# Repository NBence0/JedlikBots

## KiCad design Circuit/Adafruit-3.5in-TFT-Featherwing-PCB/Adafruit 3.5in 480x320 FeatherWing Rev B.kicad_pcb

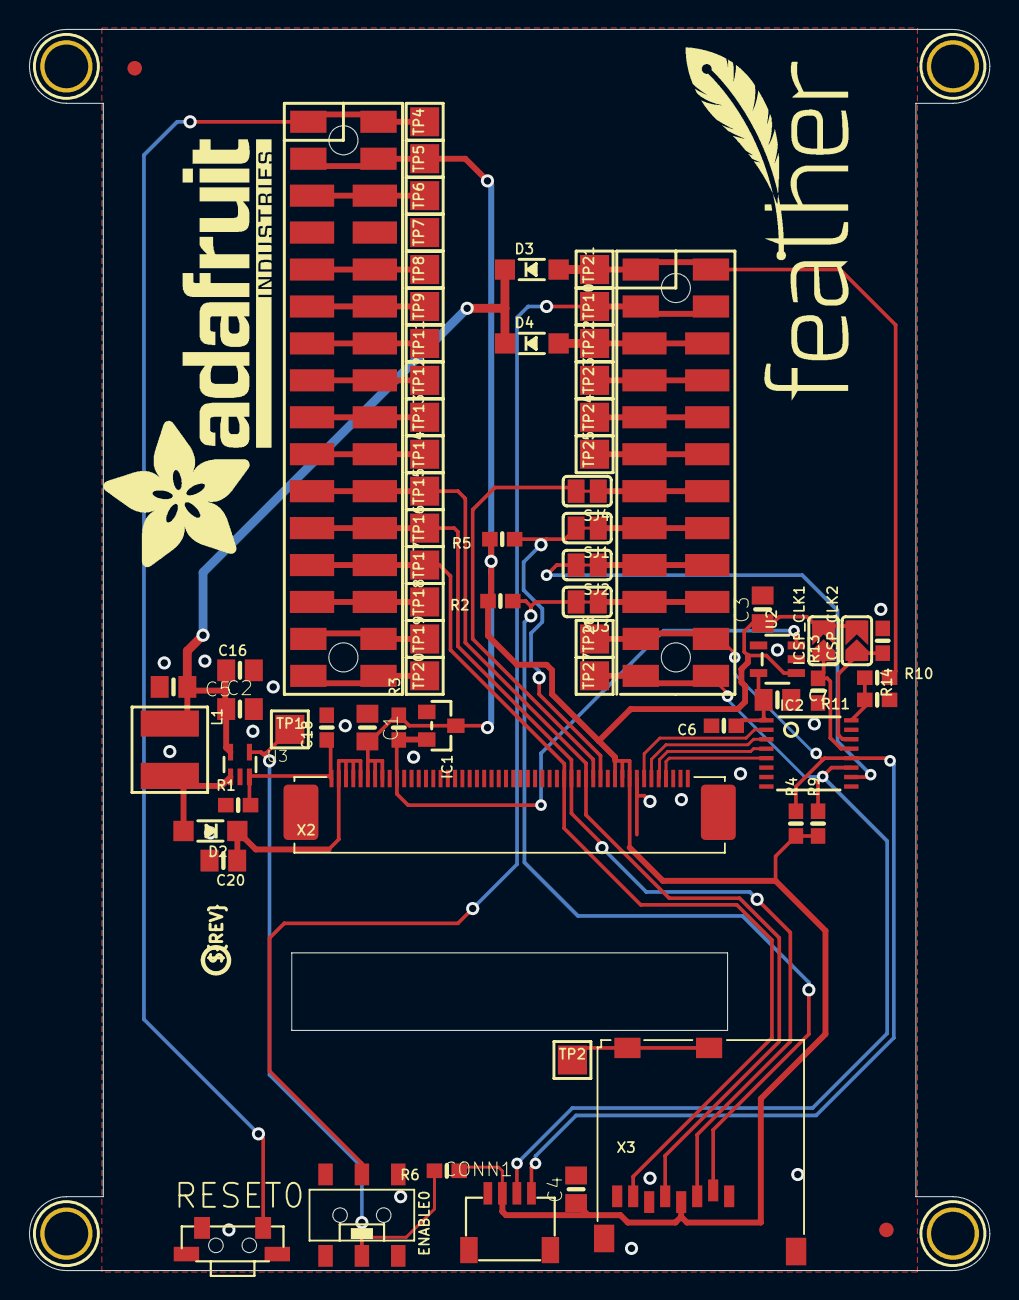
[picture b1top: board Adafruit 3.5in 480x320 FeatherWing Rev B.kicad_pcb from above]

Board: 16 copper layers, 66.0 x 85.3 mm, 92 parts (1 on the bottom side), 47 nets.

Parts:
C1, C16, C20: 1uF; 0805-NO
C2, C3, C4, C5, C7: 10uF; 0805-NO
C6, C18: 0.1uF; 0603-NO
CONN1: STEMMA_I2C_QT; JST_SH4
D2, D3, D4: MBR0540; SOD-123
ENABLE0: Slide Switch; EG1390
IC1: RESET_SUPERVISORAPX80X_SA; SOT23-WIDE
IC2: TSC2007PW; TSSOP16
ICSP_CLK1: A1; SOLDERJUMPER_ARROW_NOPASTE
ICSP_CLK2: A0; SOLDERJUMPER_ARROW_NOPASTE
L1: 6.8uH; INDUCTOR_5X5MM_NR5040_NOTHERMALS
MS2: FEATHERWING_SMTDUAL; FEATHERWING_SMT2
PLABEL0: PLABEL0
PLABEL1: PLABEL1
PLABEL2: PLABEL2
PLABEL3: PLABEL3
PLABEL4: PLABEL4
PLABEL5: PLABEL5
PLABEL6: PLABEL6
PLABEL7: PLABEL7
PLABEL8: PLABEL8
PLABEL9: PLABEL9
PLABEL10: PLABEL10
PLABEL11: PLABEL11
PLABEL12: PLABEL12
PLABEL13: PLABEL13
PLABEL14: PLABEL14
PLABEL15: PLABEL15
R1: 8.2 ohm; 0603-NO
R2, R5, R6, R10, R11: 100K; 0603-NO
R3, R4, R9, R13, R14: 10K; 0603-NO
RESET0: SPST_RA; SPST_TACTILE_RA
SJ1, SJ2, SJ3, SJ4: SOLDERJUMPER_CLOSEDWIRE
TP1, TP2, TP4, TP5, TP6, TP7, TP8, TP9, TP10, TP11, TP12, TP13, TP14, TP15, TP16, TP17, TP18, TP19, TP20, TP21, TP22, TP23, TP24, TP25, TP26, TP27: TESTPOINT_PAD_2MM
U2: AP2127K-3.3; SOT23-5
U3: TPS61169; SC70-5
U$7, U$15, U$16, U$17: MOUNTINGHOLE3.0THIN; MOUNTINGHOLE_3.0_PLATEDTHIN
U$9, U$23: FIDUCIAL_1MM
U$11: FEATHERLOGO
U$19: ADAFRUIT_TEXT_30MM
U$37: PCBFEAT-REV-040
X2: 3.5" TFT; TFT_3.5IN_320X480_50PIN
X3: MicroSD; MICROSD

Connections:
3.3V: C1.1, C3.1, C4.1, CONN1.2, IC1.3, ICSP_CLK1.2, ICSP_CLK2.2, MS2.2, MS2.2', R2.2, R3.2, R4.1, R5.2, R6.1, R9.1, TP5.P$1, U2.1, X2.6, X2.7, X2.8, X2.40, X2.41, X2.42, X3.4
+5V: C2.1, C5.1, C16.1, D3.C, D4.C, L1.P$1, U3.5
+24V: C20.1, D2.C, X2.2, X2.3, X2.4, X2.5
A: MS2.5, MS2.5', TP8.P$1
ADDR0: IC2.14, ICSP_CLK2.1, R14.2
ADDR1: IC2.13, ICSP_CLK1.1, R13.2
AREF: MS2.3, MS2.3', TP6.P$1
AUX: IC2.16, R10.1, R11.2
B: MS2.6, MS2.6', TP9.P$1
C: MS2.7, MS2.7', TP11.P$1
CARDDET: TP2.P$1, X3.CD1, X3.CD2
D: MS2.8, MS2.8', TP12.P$1
E: MS2.9, MS2.9', TP13.P$1
EN: ENABLE0.P2, MS2.27, MS2.27', TP10.P$1
F: MS2.10, MS2.10', TP14.P$1
G: MS2.16, MS2.16', TP20.P$1
GND: C1.2, C2.2, C3.2, C4.2, C5.2, C6.2, C7.2, C16.2, C18.2, C20.2, CONN1.1, CONN1.MT1, CONN1.MT2, ENABLE0.S1, ENABLE0.S2, IC1.1, IC2.6, MS2.4, MS2.4', R1.1, R11.1, R13.1, R14.1, RESET0.1, RESET0.MT1, RESET0.MT2, TP7.P$1, U2.2, U3.2, X2.43, X2.48, X2.49, X2.50, X3.6, X3.MT1, X3.MT2
H: MS2.19, MS2.19', SJ3.1
I: MS2.20, MS2.20', SJ2.1
J: MS2.21, MS2.21', SJ1.1
K: MS2.22, MS2.22', SJ4.1
L: MS2.23, MS2.23', TP25.P$1
LCD_LITE: ENABLE0.P1, R6.2, TP1.P$1, U3.4
LEDK: C18.1, R1.2, U3.3, X2.1
M: MS2.24, MS2.24', TP24.P$1
MISO: MS2.13, MS2.13', TP17.P$1, X2.33, X3.7
MOSI: MS2.12, MS2.12', TP16.P$1, X2.34, X3.3
N: MS2.25, MS2.25', TP23.P$1
unnamed: D2.A, L1.P$2, U3.1
RT_INT: IC2.10, SJ2.2
RX: MS2.14, MS2.14', TP18.P$1
SCL: CONN1.4, IC2.12, MS2.18, MS2.18', R4.2, TP26.P$1
SCLK: MS2.11, MS2.11', TP15.P$1, X2.36, X3.5
SDA: CONN1.3, IC2.11, MS2.17, MS2.17', R9.2, TP27.P$1
SD_CS: R2.1, SJ3.2, X3.2
TFT_CS: R5.1, SJ1.2, X2.38
TFT_DC: SJ4.2, X2.37
TSC_PWR: C6.1, C7.1, IC2.1, U2.5
TX: MS2.15, MS2.15', TP19.P$1
USB: D4.A, MS2.26, MS2.26', TP22.P$1
VBAT: D3.A, MS2.28, MS2.28', R10.2, TP21.P$1
XL: IC2.4, X2.46
XR: IC2.2, X2.44
YD: IC2.3, X2.45
YU: IC2.5, X2.47
~RESET: MS2.1, MS2.1', RESET0.2, TP4.P$1
~TFT_RST: IC1.2, R3.1, U2.3, X2.10

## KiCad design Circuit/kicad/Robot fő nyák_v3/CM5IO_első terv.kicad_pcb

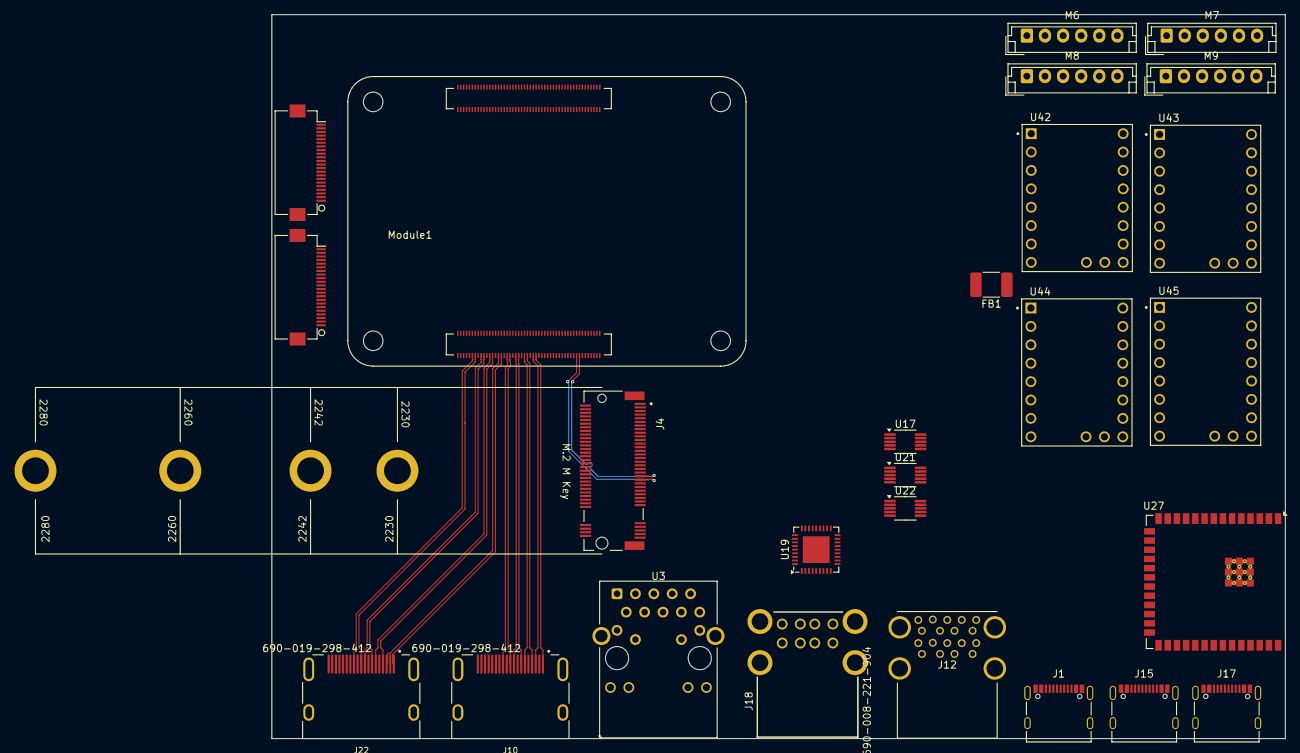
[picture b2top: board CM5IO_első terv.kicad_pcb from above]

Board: 2 copper layers, 140.0 x 100.0 mm, 26 parts (0 on the bottom side), 134 nets.

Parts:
FB1: FerriteBead 742792093; C_1812_4532Metric_Pad1.57x3.40mm_HandSolder
J1, J15, J17: USB_C_Receptacle_USB2.0_16P; USB_C_Receptacle_Palconn_UTC16-G
J4: Bus_M.2_Socket_M; M.2 M Key socket
J5, J16: Conn_01x22_Female; Hirose_FH12-22S-0.5SH_1x22-1MP_P0.50mm_Horizontal
J10, J22: 690-019-298-412; EDAC 690-019-298-412
J12: USB3_A; MTCONN_UBAF30-D2011
J18: 690-008-221-904; MOLEX_USB_67298-4090
M6, M7, M8, M9: Stepper_Motor_unipolar_6pin; JST_EH_B6B-EH-A_1x06_P2.50mm_Vertical
Module1: ComputeModule5-CM5; Raspberry-Pi-5-Compute-Module
U3: MagJack-A70-112-331N126; TRJG0926HENL
U17, U21, U22: FSUSB42MUX; MSOP-10_3x3mm_P0.5mm
U19: USB2514B-I/M2; QFN-36-1EP_6x6mm_P0.5mm_EP3.7x3.7mm
U27: ESP32-S3-WROOM-2
U42, U43, U44, U45: TMC2240_SILENTSTEPSTICK; TMC2209

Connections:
/+3.3v: Module1.84 (+3.3v_(Output)), Module1.86 (+3.3v_(Output)), U3.15 (LEDY_A), U3.17 (LEDG_A)
/+5v: Module1.77 (+5v_(Input)), Module1.79 (+5v_(Input)), Module1.81 (+5v_(Input)), Module1.83 (+5v_(Input)), Module1.85 (+5v_(Input)), Module1.87 (+5v_(Input))
/CM5_GPIO ( Ethernet, GPIO, SDCARD)/+1.8v: Module1.88 (+1.8v_(Output)), Module1.90 (+1.8v_(Output))
/CM5_GPIO ( Ethernet, GPIO, SDCARD)/CAM_GPIO0: J5.17, Module1.97 (CAM_GPIO0)
/CM5_GPIO ( Ethernet, GPIO, SDCARD)/CAM_GPIO1: J5.18, Module1.100 (CAM_GPIO1)
/CM5_GPIO ( Ethernet, GPIO, SDCARD)/TRD0_N: Module1.10 (Ethernet_Pair0_N), U3.2 (TRD0-)
/CM5_GPIO ( Ethernet, GPIO, SDCARD)/TRD0_P: Module1.12 (Ethernet_Pair0_P), U3.1 (TRD0+)
/CM5_GPIO ( Ethernet, GPIO, SDCARD)/TRD1_N: Module1.6 (Ethernet_Pair1_N), U3.6 (TRD1-)
/CM5_GPIO ( Ethernet, GPIO, SDCARD)/TRD1_P: Module1.4 (Ethernet_Pair1_P), U3.3 (TRD1+)
/CM5_GPIO ( Ethernet, GPIO, SDCARD)/TRD2_N: Module1.9 (Ethernet_Pair2_N), U3.8 (TRD2-)
/CM5_GPIO ( Ethernet, GPIO, SDCARD)/TRD2_P: Module1.11 (Ethernet_Pair2_P), U3.7 (TRD2+)
/CM5_GPIO ( Ethernet, GPIO, SDCARD)/TRD3_N: Module1.5 (Ethernet_Pair3_N), U3.10 (TRD3-)
/CM5_GPIO ( Ethernet, GPIO, SDCARD)/TRD3_P: Module1.3 (Ethernet_Pair3_P), U3.9 (TRD3+)
/CM5_HighSpeed/+3.3v_DSI: J5.22, J16.22
/CM5_HighSpeed/DPHY0_C_N: J5.8, Module1.127 (MIPI0_C_N)
/CM5_HighSpeed/DPHY0_C_P: J5.9, Module1.129 (MIPI0_C_P)
/CM5_HighSpeed/DPHY0_D0_N: J5.2, Module1.115 (MIPI0_D0_N)
/CM5_HighSpeed/DPHY0_D0_P: J5.3, Module1.117 (MIPI0_D0_P)
/CM5_HighSpeed/DPHY0_D1_N: J5.5, Module1.121 (MIPI0_D1_N)
/CM5_HighSpeed/DPHY0_D1_P: J5.6, Module1.123 (MIPI0_D1_P)
/CM5_HighSpeed/DPHY0_D2_N: J5.11, Module1.133 (MIPI0_D2_N)
/CM5_HighSpeed/DPHY0_D2_P: J5.12, Module1.135 (MIPI0_D2_P)
/CM5_HighSpeed/DPHY0_D3_N: J5.14, Module1.139 (MIPI0_D3_N)
/CM5_HighSpeed/DPHY0_D3_P: J5.15, Module1.141 (MIPI0_D3_P)
/CM5_HighSpeed/DPHY1_C_N: J16.8, Module1.187 (MIPI1_C_N)
/CM5_HighSpeed/DPHY1_C_P: J16.9, Module1.189 (MIPI1_C_P)
/CM5_HighSpeed/DPHY1_D0_N: J16.2, Module1.175 (MIPI1_D0_N)
/CM5_HighSpeed/DPHY1_D0_P: J16.3, Module1.177 (MIPI1_D0_P)
/CM5_HighSpeed/DPHY1_D1_N: J16.5, Module1.181 (MIPI1_D1_N)
/CM5_HighSpeed/DPHY1_D1_P: J16.6, Module1.183 (MIPI1_D1_P)
/CM5_HighSpeed/DPHY1_D2_N: J16.11, Module1.193 (MIPI1_D2_N)
/CM5_HighSpeed/DPHY1_D2_P: J16.12, Module1.195 (MIPI1_D2_P)
/CM5_HighSpeed/DPHY1_D3_N: J16.14, Module1.194 (MIPI1_D3_N)
/CM5_HighSpeed/DPHY1_D3_P: J16.15, Module1.196 (MIPI1_D3_P)
/CM5_HighSpeed/HDMI0_CEC: J22.13 (CEC), Module1.151 (HDMI0_CEC)
/CM5_HighSpeed/HDMI0_CK_N: J22.12 (CK-), Module1.190 (HDMI0_CLK_N)
/CM5_HighSpeed/HDMI0_CK_P: J22.10 (CK+), Module1.188 (HDMI0_CLK_P)
/CM5_HighSpeed/HDMI0_D0_N: J22.9 (D0-), Module1.184 (HDMI0_TX0_N)
/CM5_HighSpeed/HDMI0_D0_P: J22.7 (D0+), Module1.182 (HDMI0_TX0_P)
/CM5_HighSpeed/HDMI0_D1_N: J22.6 (D1-), Module1.178 (HDMI0_TX1_N)
/CM5_HighSpeed/HDMI0_D1_P: J22.4 (D1+), Module1.176 (HDMI0_TX1_P)
/CM5_HighSpeed/HDMI0_D2_N: J22.3 (D2-), Module1.172 (HDMI0_TX2_N)
/CM5_HighSpeed/HDMI0_D2_P: J22.1 (D2+), Module1.170 (HDMI0_TX2_P)
/CM5_HighSpeed/HDMI0_HOTPLUG: J22.19 (HPD/HEAC-), Module1.153 (HDMI0_HOTPLUG)
/CM5_HighSpeed/HDMI0_SCL: J22.15 (SCL), Module1.200 (HDMI0_SCL)
/CM5_HighSpeed/HDMI0_SDA: J22.16 (SDA), Module1.199 (HDMI0_SDA)
/CM5_HighSpeed/HDMI1_CEC: J10.13 (CEC), Module1.149 (HDMI1_CEC)
/CM5_HighSpeed/HDMI1_CK_N: J10.12 (CK-), Module1.166 (HDMI1_CLK_N)
/CM5_HighSpeed/HDMI1_CK_P: J10.10 (CK+), Module1.164 (HDMI1_CLK_P)
/CM5_HighSpeed/HDMI1_D0_N: J10.9 (D0-), Module1.160 (HDMI1_TX0_N)
/CM5_HighSpeed/HDMI1_D0_P: J10.7 (D0+), Module1.158 (HDMI1_TX0_P)
/CM5_HighSpeed/HDMI1_D1_N: J10.6 (D1-), Module1.154 (HDMI1_TX1_N)
/CM5_HighSpeed/HDMI1_D1_P: J10.4 (D1+), Module1.152 (HDMI1_TX1_P)
/CM5_HighSpeed/HDMI1_D2_N: J10.3 (D2-), Module1.148 (HDMI1_TX2_N)
/CM5_HighSpeed/HDMI1_D2_P: J10.1 (D2+), Module1.146 (HDMI1_TX2_P)
/CM5_HighSpeed/HDMI1_HOTPLUG: J10.19 (HPD/HEAC-), Module1.143 (HDMI1_HOTPLUG)
/CM5_HighSpeed/HDMI1_SCL: J10.15 (SCL), Module1.147 (HDMI1_SCL)
/CM5_HighSpeed/HDMI1_SDA: J10.16 (SDA), Module1.145 (HDMI1_SDA)
/CM5_HighSpeed/HDMI_5v: J10.18 (+5V), J22.18 (+5V)
/CM5_HighSpeed/PCIE_CLK_N: J4.53 (REFCLKn), Module1.112 (PCIe_CLK_N)
/CM5_HighSpeed/PCIE_CLK_P: J4.55 (REFCLKp), Module1.110 (PCIe_CLK_P)
/CM5_HighSpeed/PCIE_RX_N: J4.43 (PETp0), Module1.118 (PCIe_RX_N)
/CM5_HighSpeed/PCIE_RX_P: J4.41 (PETn0), Module1.116 (PCIe_RX_P)
/CM5_HighSpeed/PCIE_TX_N: J4.49 (PERp0), Module1.124 (PCIe_TX_N)
/CM5_HighSpeed/PCIE_TX_P: J4.47 (PERn0), Module1.122 (PCIe_TX_P)
/CM5_HighSpeed/PCIE_nCLKREQ: J4.52 (~CLKREQ), Module1.102 (PCIe_nCLKREQ)
/CM5_HighSpeed/PCIE_nRST: J4.50 (~PERST), Module1.109 (PCIe_nRST)
/CM5_HighSpeed/PCIE_nWAKE: J4.54 (~PEWAKE), Module1.104 (PCIE_nWAKE)
/CM5_HighSpeed/SCL0: J5.20, Module1.80 (SCL0)
/CM5_HighSpeed/SDA0: J5.21, Module1.82 (SDA0)
/CM5_HighSpeed/USB2_N: Module1.103 (USB2_N), U17.4 (D_N)
/CM5_HighSpeed/USB2_P: Module1.105 (USB2_P), U17.3 (D_P)
/CM5_HighSpeed/USB3-0-D_N: J12.A2 (D-), Module1.136 (USB3-0-D_N)
/CM5_HighSpeed/USB3-0-D_P: J12.A3 (D+), Module1.134 (USB3-0-D_P)
/CM5_HighSpeed/USB3-0-RX_N: J12.A6 (SSRX+), Module1.128 (USB3-0-RX_N)
/CM5_HighSpeed/USB3-0-RX_P: J12.A5 (SSRX-), Module1.130 (USB3-0-RX_P)
/CM5_HighSpeed/USB3-0-TX_N: J12.A9 (SSTX+), Module1.140 (USB3-0-TX_N)
/CM5_HighSpeed/USB3-0-TX_P: J12.A8 (SSTX-), Module1.142 (USB3-0-TX_P)
/CM5_HighSpeed/USB3-1-D_N: J12.B2 (D-), Module1.165 (USB3-1-D_N)
/CM5_HighSpeed/USB3-1-D_P: J12.B3 (D+), Module1.163 (USB3-1-D_P)
/CM5_HighSpeed/USB3-1-RX_N: J12.B6 (SSRX+), Module1.157 (USB3-1-RX_N)
/CM5_HighSpeed/USB3-1-RX_P: J12.B5 (SSRX-), Module1.159 (USB3-1-RX_P)
/CM5_HighSpeed/USB3-1-TX_N: J12.B9 (SSTX+), Module1.169 (USB3-1-TX_N)
/CM5_HighSpeed/USB3-1-TX_P: J12.B8 (SSTX-), Module1.171 (USB3-1-TX_P)
/CM5_HighSpeed/USBOTG_ID: Module1.101 (USB_OTG_ID), U17.2 (SEL)
/CM5_HighSpeed/VBUS: J12.A1 (VBUS), J12.B1 (VBUS)
/PCIe-M2/M2_3v3: J4.2 (3.3V), J4.4 (3.3V), J4.12 (3.3V), J4.14 (3.3V), J4.16 (3.3V), J4.18 (3.3V), J4.70 (3.3V), J4.72 (3.3V), J4.74 (3.3V)
/USB2-HUB/+3.3v: U17.1 (VCC), U19.5 (VDDA33), U19.10 (VDDA33), U19.15 (VDD33), U19.23 (VDD33), U19.27 (VBUS_DET), U19.29 (VDDA33), U19.36 (VDDA33), U21.1 (VCC), U22.1 (VCC)
/USB2-HUB/ESP_usbD+: U21.3 (D_P), U27.14 (USB_D+/IO20)
/USB2-HUB/ESP_usbD-: U21.4 (D_N), U27.13 (USB_D-/IO19)
/USB2-HUB/HD1_N: J18.2 (D-`), U19.1 (USBDM_DN1/PRT_DIS_M1)
/USB2-HUB/HD1_P: J18.3 (D+`), U19.2 (USBDP_DN1/PRT_DIS_P1)
/USB2-HUB/HD2_N: J18.6 (D-), U19.3 (USBDM_DN2/PRT_DIS_M2)
/USB2-HUB/HD2_P: J18.7 (D+), U19.4 (USBDP_DN2/PRT_DIS_P2)
/USB2-HUB/HD3_N: U19.6 (USBDM_DN3/PRT_DIS_M3), U22.6 (HSD0_M)
/USB2-HUB/HD3_P: U19.7 (USBDP_DN3/PRT_DIS_P3), U22.7 (HSD0_P)
/USB2-HUB/HD4_N: U19.8 (USBDM_DN4/PRT_DIS_M4), U21.6 (HSD0_M)
/USB2-HUB/HD4_P: U19.9 (USBDP_DN4/PRT_DIS_P4), U21.7 (HSD0_P)
/USB2-HUB/USBD_N: J1.A6 (D+), J1.B6 (D+), U17.8 (HSD1_M)
/USB2-HUB/USBD_P: J1.A7 (D-), J1.B7 (D-), U17.9 (HSD1_P)
/USB2-HUB/USBH_N: U17.6 (HSD0_M), U19.30 (USBDM_UP)
/USB2-HUB/USBH_P: U17.7 (HSD0_P), U19.31 (USBDP_UP)
/USB2-HUB/VBUS: J18.1 (VBUS`), J18.5 (VBUS)
/USB2-HUB/nEXTRST: J1.A4 (VBUS), J1.A9 (VBUS), J1.B4 (VBUS), J1.B9 (VBUS)
/USB2-HUB/nOCS1: U19.13 (OCS_N1), U19.17 (OCS_N2), U19.19 (OCS_N3), U19.21 (OCS_N4)
/YD-ESP32-S3/4x tmc5160/TMC_GND: FB1.1, U42.1 (GND), U42.7 (GND), U43.1 (GND), U43.7 (GND), U44.1 (GND), U44.7 (GND), U45.1 (GND), U45.7 (GND)
GND: FB1.2, J1.A1 (GND), J1.A12 (GND), J1.B1 (GND), J1.B12 (GND), J1.S1 (SHIELD), J4.1 (GND), J4.3 (GND), J4.9 (GND), J4.15 (GND), J4.21 (GND), J4.27 (GND), J4.33 (GND), J4.39 (GND), J4.45 (GND), J4.51 (GND), J4.57 (GND), J4.71 (GND), J4.73 (GND), J4.75 (GND), J4.M1 (GND2230), J4.M2 (GND2242), J4.M3 (GND2260), J4.M4 (GND2280), J4.S1, J4.S2, J5.1, J5.4, J5.7, J5.10, J5.13, J5.16, J5.19, J10.2 (D2S), J10.5 (D1S), J10.8 (D0S), J10.11 (CKS), J10.17 (GND), J10.SH1 (SH), J10.SH2 (SH), J10.SH3 (SH), J10.SH4 (SH), J12.10 (SHIELD), J12.A4 (GND), J12.A7 (DRAIN), J12.B4 (GND), J12.B7 (DRAIN), J15.A1 (GND), J15.A12 (GND), J15.B1 (GND), J15.B12 (GND), J15.S1 (SHIELD), J16.1, J16.4, J16.7, J16.10, J16.13, J16.16, J16.19, J17.A1 (GND), J17.A12 (GND), J17.B1 (GND), J17.B12 (GND), J17.S1 (SHIELD), J18.4 (GND`), J18.8 (GND), J18.MT1, J18.MT2, J18.MT3, J18.MT4, J22.2 (D2S), J22.5 (D1S), J22.8 (D0S), J22.11 (CKS), J22.17 (GND), J22.SH1 (SH), J22.SH2 (SH), J22.SH3 (SH), J22.SH4 (SH), Module1.1 (GND), Module1.2 (GND), Module1.7 (GND), Module1.8 (GND), Module1.13 (GND), Module1.14 (GND), Module1.22 (GND), Module1.23 (GND), Module1.32 (GND), Module1.33 (GND), Module1.42 (GND), Module1.43 (GND), Module1.52 (GND), Module1.53 (GND), Module1.59 (GND), Module1.60 (GND), Module1.65 (GND), Module1.66 (GND), Module1.71 (GND), Module1.74 (GND), Module1.98 (GND), Module1.107 (GND), Module1.108 (GND), Module1.113 (GND), Module1.114 (GND), Module1.119 (GND), Module1.120 (GND), Module1.125 (GND), Module1.126 (GND), Module1.131 (GND), Module1.132 (GND), Module1.137 (GND), Module1.138 (GND), Module1.144 (GND), Module1.150 (GND), Module1.155 (GND), Module1.156 (GND), Module1.161 (GND), Module1.162 (GND), Module1.167 (GND), Module1.168 (GND), Module1.173 (GND), Module1.174 (GND), Module1.179 (GND), Module1.180 (GND), Module1.185 (GND), Module1.186 (GND), Module1.191 (GND), Module1.192 (GND), Module1.197 (GND), Module1.198 (GND), U3.19 (SHIELD), U3.20 (SHIELD), U17.5 (GND), U17.10 (nOE), U19.37 (VSS), U21.5 (GND), U21.10 (nOE), U22.5 (GND), U22.10 (nOE), U27.1 (GND), U27.40 (GND), U27.41 (GND)
unnamed: U3.4 (CT), U3.5 (CT)
unnamed: J15.A4 (VBUS), J15.A9 (VBUS), J15.B4 (VBUS), J15.B9 (VBUS)
unnamed: J17.A4 (VBUS), J17.A9 (VBUS), J17.B4 (VBUS), J17.B9 (VBUS)
unnamed: M6.3 (-), U42.3 (M1B)
unnamed: M7.3 (-), U43.3 (M1B)
unnamed: M8.3 (-), U44.3 (M1B)
unnamed: M9.3 (-), U45.3 (M1B)
unnamed: J15.A7 (D-), J15.B7 (D-), U21.8 (HSD1_M)
unnamed: J15.A6 (D+), J15.B6 (D+), U21.9 (HSD1_P)
unnamed: J17.A7 (D-), J17.B7 (D-), U22.8 (HSD1_M)
unnamed: J17.A6 (D+), J17.B6 (D+), U22.9 (HSD1_P)
unnamed: M6.6, U42.6 (M1A)
unnamed: M6.4, U42.5 (M2A)
unnamed: M6.1, U42.4 (M2B)
unnamed: M7.6, U43.6 (M1A)
unnamed: M7.4, U43.5 (M2A)
unnamed: M7.1, U43.4 (M2B)
unnamed: M8.6, U44.6 (M1A)
unnamed: M8.4, U44.5 (M2A)
unnamed: M8.1, U44.4 (M2B)
unnamed: M9.6, U45.6 (M1A)
unnamed: M9.4, U45.5 (M2A)
unnamed: M9.1, U45.4 (M2B)
TMC_MISO: U42.11 (MISO), U43.11 (MISO), U44.11 (MISO), U45.11 (MISO)
TMC_MOSI: U42.15 (MOSI), U43.15 (MOSI), U44.15 (MOSI), U45.15 (MOSI)
TMC_SPI_CLK: U42.14 (Spi_clk), U43.14 (Spi_clk), U44.14 (Spi_clk), U45.14 (Spi_clk)
TMC_VIO: U42.2 (VIO/VDD), U43.2 (VIO/VDD), U44.2 (VIO/VDD), U45.2 (VIO/VDD)
